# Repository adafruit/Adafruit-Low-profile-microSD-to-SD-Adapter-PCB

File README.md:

## Adafruit Low profile microSD to SD Adapter PCB (discontinued)
<a href="http://www.adafruit.com/products/966"><br/>
Click here to view on the Adafruit website
</a>

PCB files for the Adafruit Low-profile microSD to SD Adapter. Format is EagleCAD schematic and board layout
- https://www.adafruit.com/product/966

This product has been discontinued.

### License

Adafruit invests time and resources providing this open source design, please support Adafruit and open-source hardware by purchasing products from [Adafruit.com](https://www.adafruit.com)!

Creative Commons Attribution, Share-Alike license, check license.txt for more information All text above must be included in any redistribution - 
See license.txt for more information.

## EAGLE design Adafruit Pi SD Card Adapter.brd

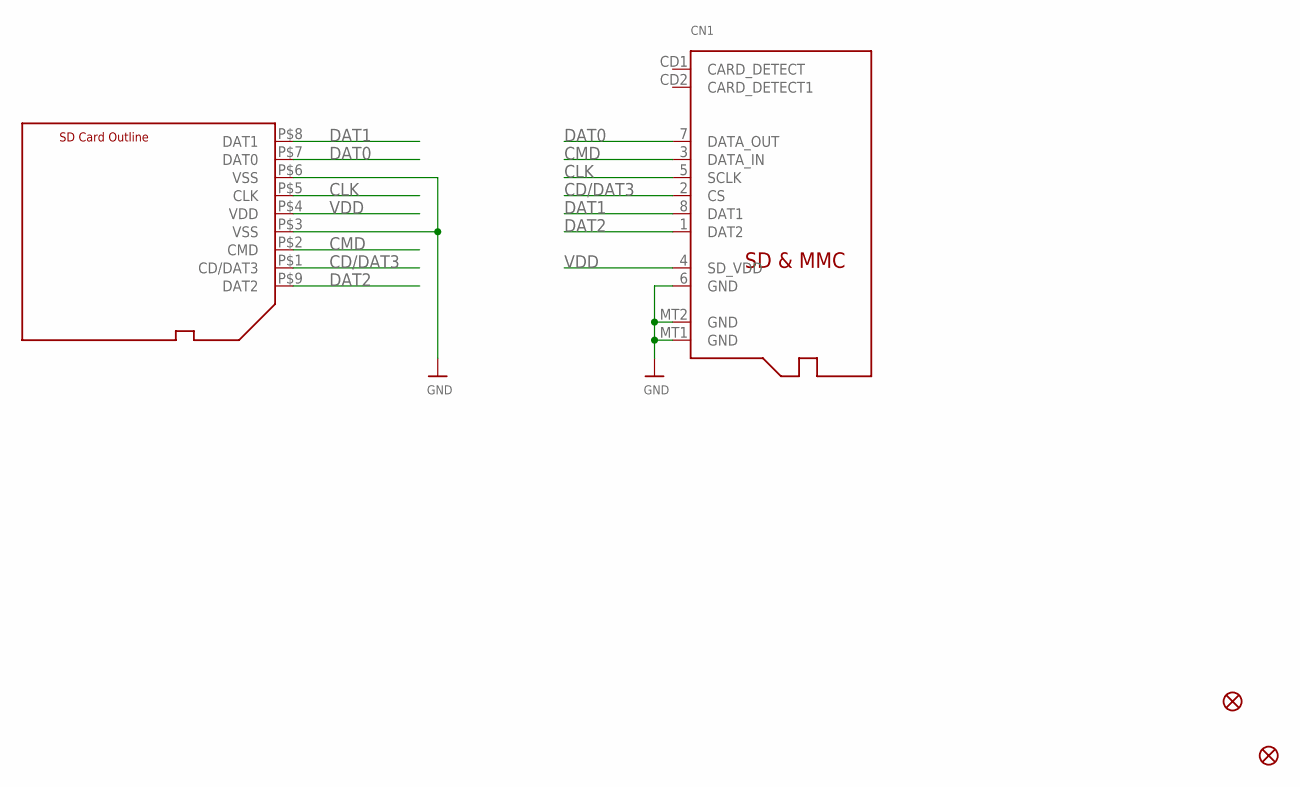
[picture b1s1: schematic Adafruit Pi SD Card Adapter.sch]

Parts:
CN1: MICROSD
FID1, FID2: FIDUCIAL1X2.5; FIDUCIAL-1X2.5
U$2: SDCARD_PCBCARRIERTDOCU; SDCARD_PCBCARRIER_DOCU

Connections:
CD/DAT3: CN1.2 (CS), U$2.P$1 (CD/DAT3)
CLK: CN1.5 (SCLK), U$2.P$5 (CLK)
CMD: CN1.3 (DATA_IN), U$2.P$2 (CMD)
DAT0: CN1.7 (DATA_OUT), U$2.P$7 (DAT0)
DAT1: CN1.8 (DAT1), U$2.P$8 (DAT1)
DAT2: CN1.1 (DAT2), U$2.P$9 (DAT2)
GND: CN1.6 (GND), CN1.MT1 (GND), CN1.MT2 (GND), U$2.P$3 (VSS), U$2.P$6 (VSS)
VDD: CN1.4 (SD_VDD), U$2.P$4 (VDD)

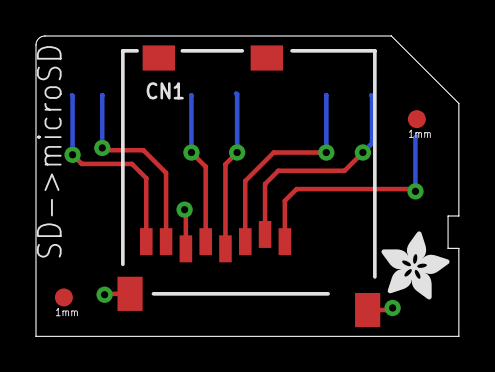
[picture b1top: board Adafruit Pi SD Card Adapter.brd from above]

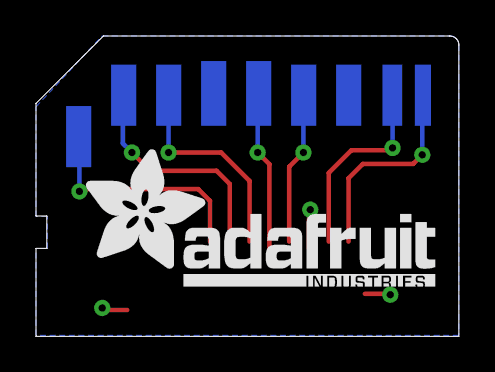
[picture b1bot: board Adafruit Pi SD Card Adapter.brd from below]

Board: 2 copper layers, 23.5 x 16.7 mm, 6 parts (2 on the bottom side), 8 nets.

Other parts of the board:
U$5: ADAFRUIT_3.5MM
U$6: ADAFRUIT_TEXT_20MM

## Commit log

2016-10-06 init

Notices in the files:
parts and their libraries:
microbuilder: This work is placed in the public domain, and may be freely used for commercial and non-commercial work with the following conditions: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
